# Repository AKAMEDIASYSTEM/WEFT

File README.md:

# WEFT
#### Experiments in electrovibration interaction strategies, inspired by Disney Research papers "Tesla Touch" and "Revel"

Here are the papers I am trying to implement here:
http://www.ivanpoupyrev.com/e-library/2010/teslatouchUIST2010.pdf

http://www.disneyresearch.com/wp-content/uploads/REVEL.pdf

### Summary
Basically, the papers describe a way to augment surfaces with _dynamically changeable tactile properties_ - a surface can change from sticky to slippery basically at will.

### Status
This work is incomplete and ongoing - for one thing, while the circuit decribed here works, I have yet to implement current-sensing feedback as described in the papers. I'm eager to accomplish this because it allows normalization of sensation across people, skin moistures, and time.

### Why I am interested
I'm interested in experimenting with this technology as applied to various notification strategies, particularly on mobile and wearable devices.
I would like to develop interactions in which a person queries a "stack" of stuff waiting for them, rather than being interrupted by a push notification.
The appeal of this technology in this application is that it's totally silent and able to be done without interrupting the person's conversation by stealing focus.
If this technology is implemented on the back of a mobile device, for example, simply rubbing a finger along the back of the phone is all that is needed to see the magnitude of my "stack."
Of course, "stack" can be many things: number of unread emails, number of to-do items, number of places of interest very near me, and so on.

### This repository
The purpose of this repo is to make my work shareable - I had a fair amount of trouble trying to go from the research paper to a safe, working circuit, and I'm hoping to save others some work.

The circuitboard isn't what I would put onto a phone - it is instead a platform for trying out different waveforms, intensities, and so on.

The intent is that you will use the board to figure out the correct implementation details and then generate your own board with a more appropriate layout.

### Requirements
You should follow the BOM pretty precisely unless you know what you are doing. The circuit is designed to work with a 9v battery and I will be trying to allow smaller/more power supplies to work with it. The microcontroller is a Teensy 3.1

### Thanks
I'm so grateful to Disney Research, Ivan Poupyrev, Olivier Bau, and others who worked on the papers for making their work available - I never would have known aobut this cool phoneomenon without their shared work! Thanks as well to nytlabs for supporting my explorations and letting me share in kind.

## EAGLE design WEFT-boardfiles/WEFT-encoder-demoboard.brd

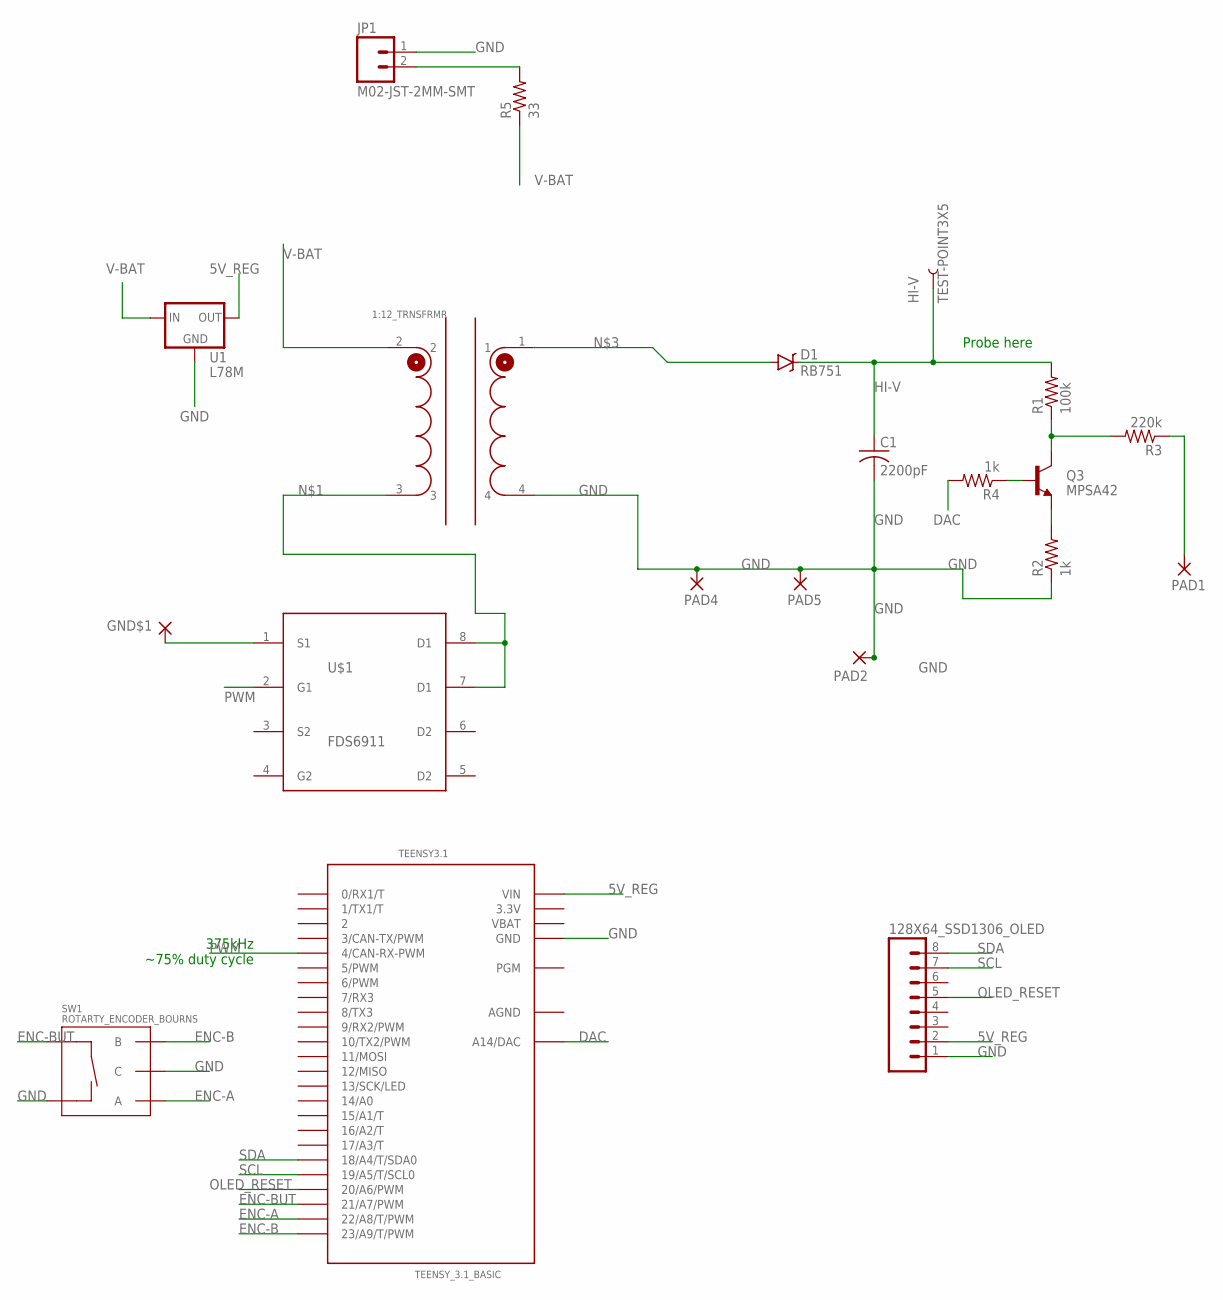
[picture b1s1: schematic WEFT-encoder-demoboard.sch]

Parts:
1:12_TRNSFRMR: PA0367
128X64_SSD1306_OLED: M08LOCK; 1X08_LOCK
C1: 2200pF; C1812
D1: RB751; TO263
GND$1: WIREPADSMD5-2,5; 5-2,5
HI-V: TEST-POINT3X5; PAD.03X.05
JP1: M02-JST-2MM-SMT; JST-2-SMD
PAD1, PAD2, PAD4, PAD5: WIREPADSMD5-2,5; 5-2,5
Q3: MPSA42; TO-92
R1: 100k; R2010
R2, R4: 1k; 1206
R3: 220k; R2010
R5: 33; 1206
SW1: ROTARTY_ENCODER_BOURNS; ROTARY_ENC_PLAIN_BOURNS
TEENSY3.1: TEENSY_3.1_BASIC
U1: L78M; DPAK
U$1: FDS6911; SO8

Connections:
3.3V: TEENSY3.1.3.3V
5V_REG: 128X64_SSD1306_OLED.2, TEENSY3.1.VIN, U1.3 (OUT)
AGND: TEENSY3.1.AGND
DAC: R4.2, TEENSY3.1.A14 (A14/DAC)
ENC-A: SW1.A, TEENSY3.1.22/A8 (22/A8/T/PWM)
ENC-B: SW1.B, TEENSY3.1.23/A9 (23/A9/T/PWM)
ENC-BUT: SW1.SW+, TEENSY3.1.21/A7 (21/A7/PWM)
GND: 1:12_TRNSFRMR.4, 128X64_SSD1306_OLED.1, C1.2, GND$1.1, JP1.1 (2), PAD2.1, PAD4.1, PAD5.1, R2.1, SW1.C, SW1.SW-, TEENSY3.1.GND, TEENSY3.1.GND1 (GND), U1.4 (GND), U$1.1 (S1)
HI-V: C1.1, D1.1 (C), HI-V.P$1, R1.2
unnamed: 1:12_TRNSFRMR.3, U$1.7 (D1), U$1.8 (D1)
unnamed: 1:12_TRNSFRMR.1, D1.2 (A)
unnamed: JP1.2 (1), R5.2
unnamed: Q3.1 (C), R1.1, R3.2
unnamed: Q3.3 (E), R2.2
unnamed: Q3.2 (B), R4.1
OLED_RESET: 128X64_SSD1306_OLED.5, TEENSY3.1.20/A6 (20/A6/PWM)
PAD: PAD1.1, R3.1
PWM: TEENSY3.1.4 (4/CAN-RX-PWM), U$1.2 (G1)
SCL: 128X64_SSD1306_OLED.7, TEENSY3.1.19/A5 (19/A5/T/SCL0)
SDA: 128X64_SSD1306_OLED.8, TEENSY3.1.18/A4 (18/A4/T/SDA0)
V-BAT: 1:12_TRNSFRMR.2, R5.1, U1.1 (IN)
VBAT: TEENSY3.1.VBAT

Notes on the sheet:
Probe here
375kHz ~75% duty cycle

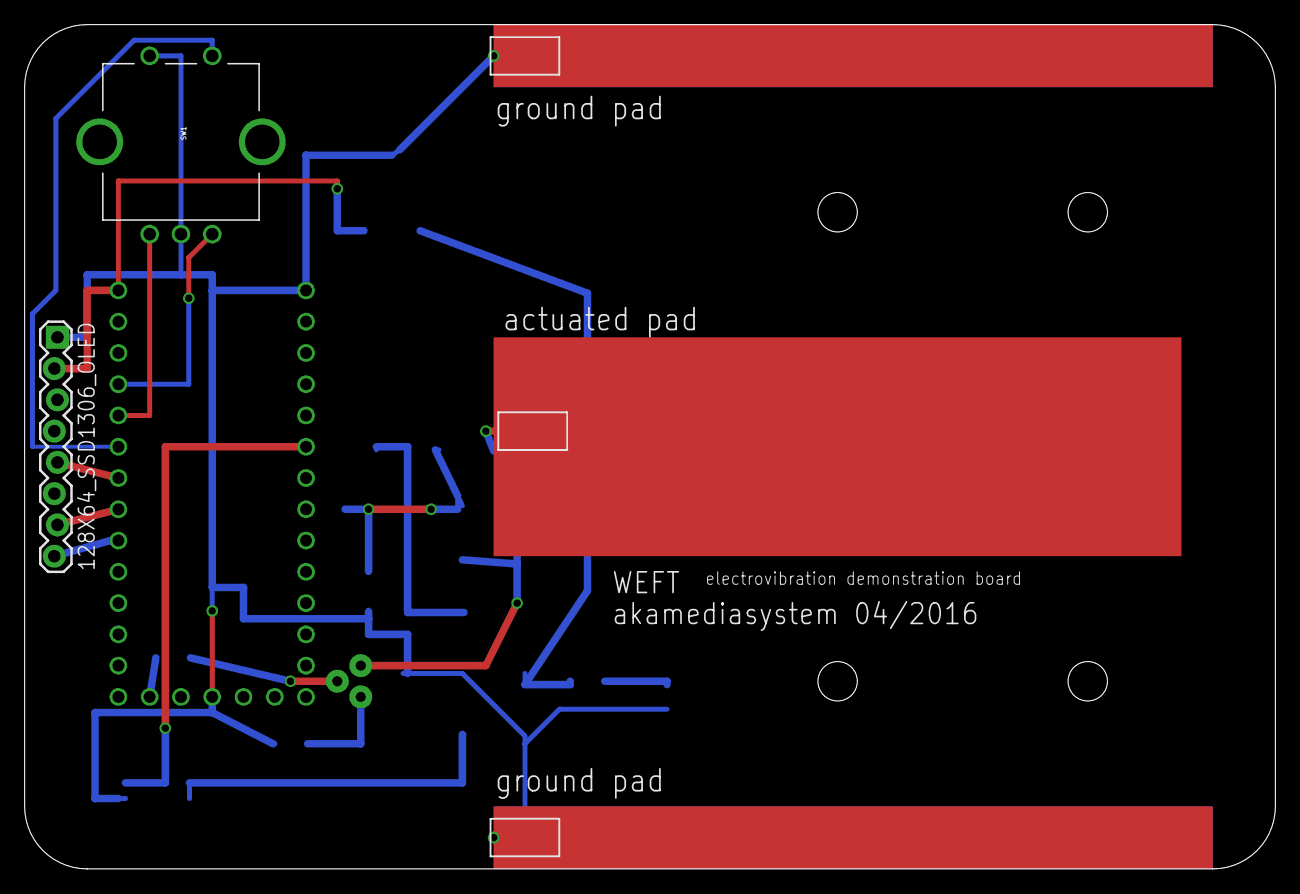
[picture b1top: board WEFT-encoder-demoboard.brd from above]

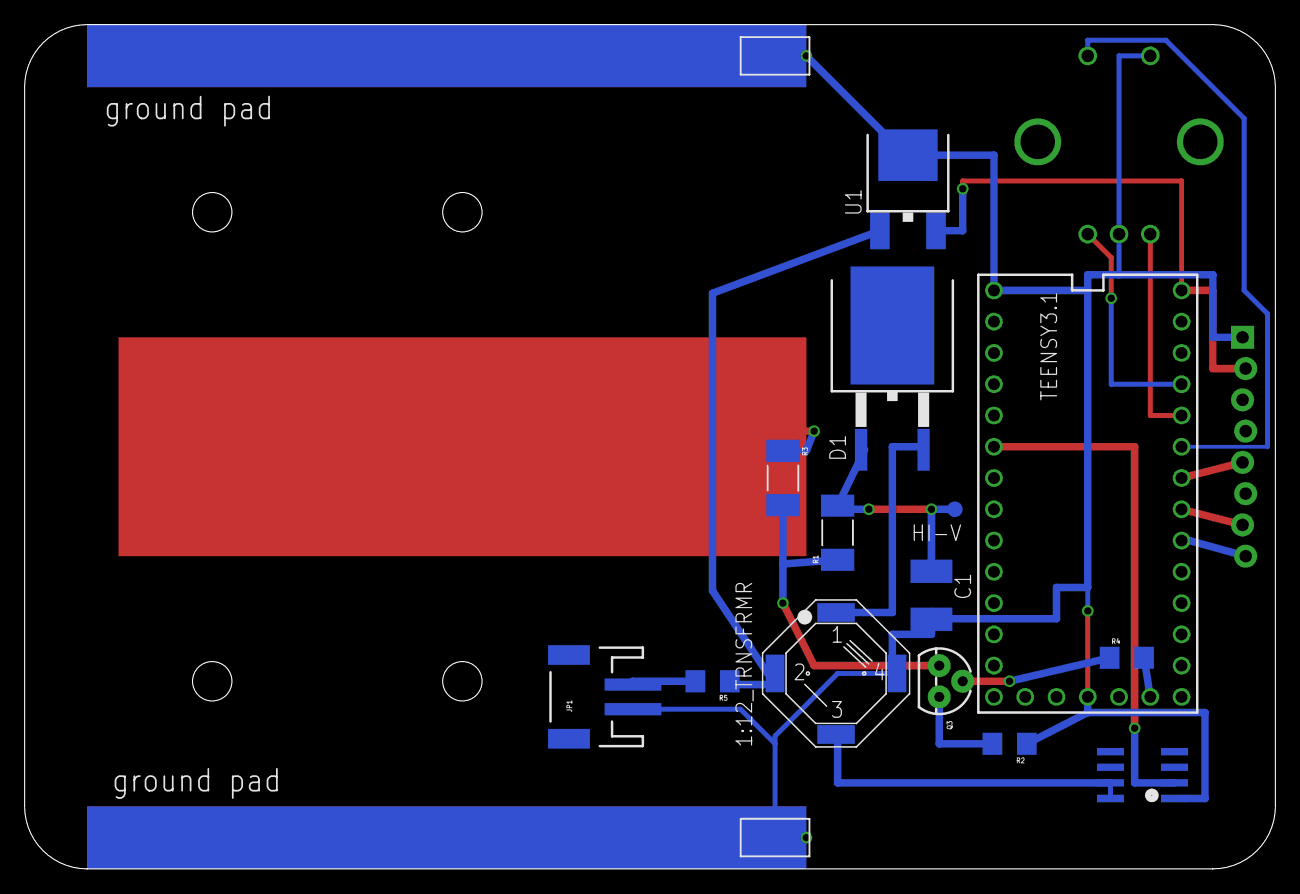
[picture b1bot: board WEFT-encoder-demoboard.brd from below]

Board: 2 copper layers, 101.6 x 68.6 mm, 21 parts (16 on the bottom side), 19 nets.

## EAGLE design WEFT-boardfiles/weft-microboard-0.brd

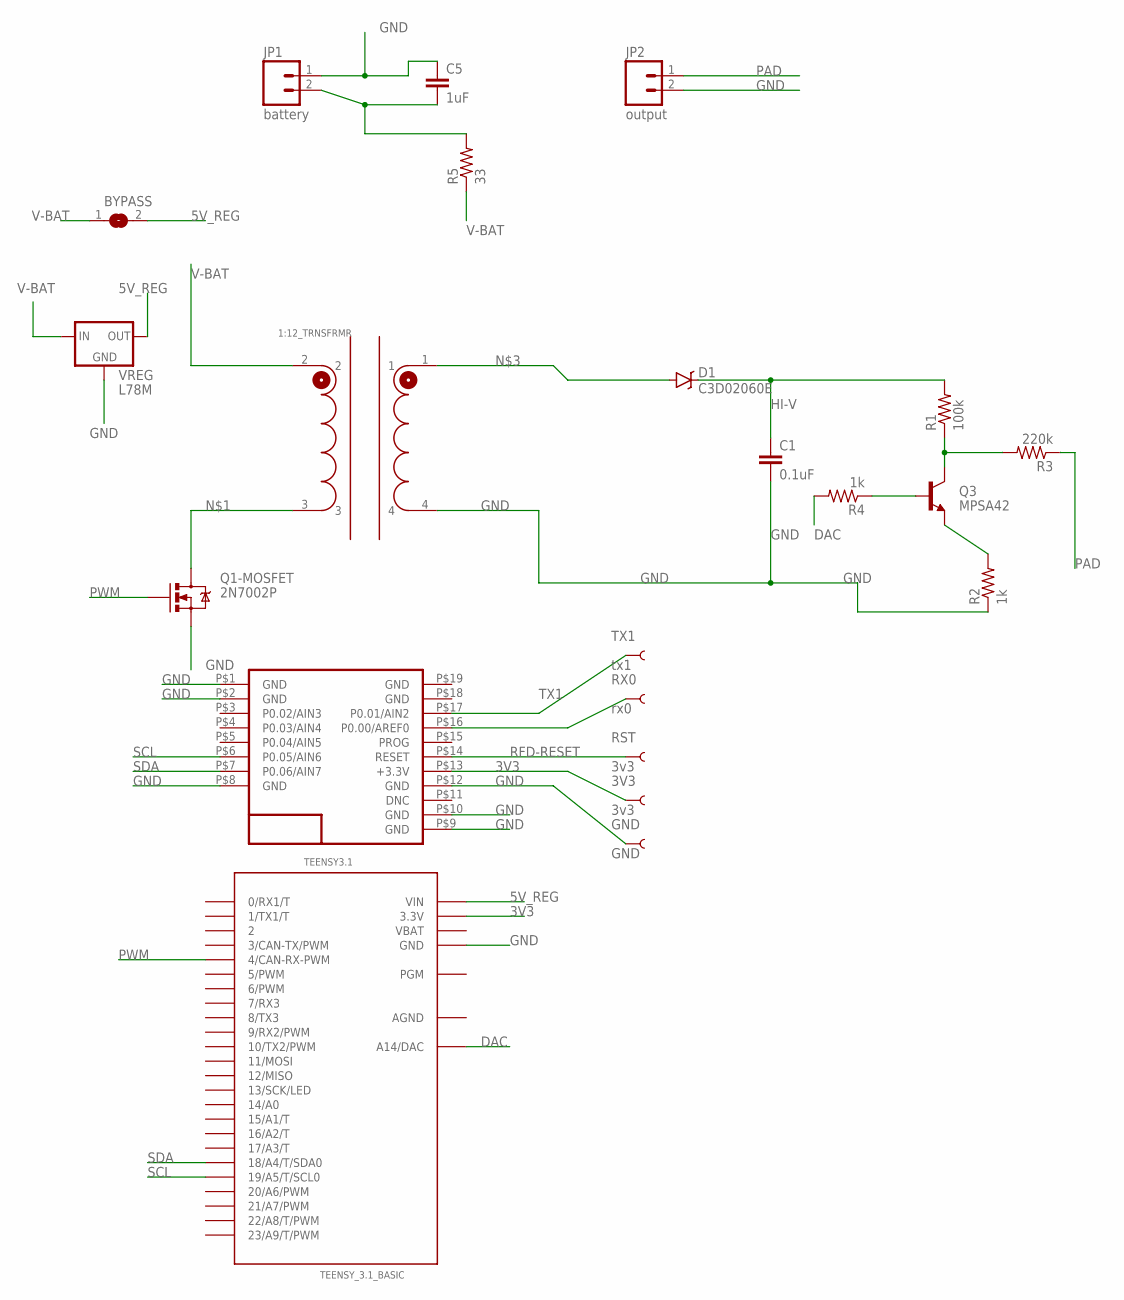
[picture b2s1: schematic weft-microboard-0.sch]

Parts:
1:12_TRNSFRMR: PA0367
3V3: 3v3; PAD.03X.03
BYPASS: SJ
C1: 0.1uF; 0805
C5: 1uF; 0805
D1: C3D02060E; TO252
GND: GND; PAD.03X.03
JP1: battery; JST-2-SMD
JP2: output; JST-2-SMD
Q1-MOSFET: 2N7002P; SOT23-3
Q3: MPSA42; SOT23-3
R1: 100k; 1206
R2, R4: 1k; 0805
R3: 220k; 1206
R5: 33; 0805
RFDUINO: RFD22301; RFD21733
RST: 3v3; PAD.03X.03
RX0: rx0; PAD.03X.03
TEENSY3.1: TEENSY_3.1_BASIC
TX1: tx1; PAD.03X.03
VREG: L78M; DPAK

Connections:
3V3: 3V3.P$1, RFDUINO.P$13 (+3.3V), TEENSY3.1.3.3V, TEENSY3.1.3.3V1 (3.3V)
5V_REG: BYPASS.2, TEENSY3.1.VIN, VREG.3 (OUT)
AGND: TEENSY3.1.AGND
DAC: R4.2, TEENSY3.1.A14 (A14/DAC)
EMIT: Q3.2 (E), R2.2
GND: 1:12_TRNSFRMR.4, C1.2, C5.1, GND.P$1, JP1.1 (2), JP2.2 (1), Q1-MOSFET.2 (S), R2.1, RFDUINO.P$1 (GND), RFDUINO.P$2 (GND), RFDUINO.P$8 (GND), RFDUINO.P$9 (GND), RFDUINO.P$10 (GND), RFDUINO.P$12 (GND), TEENSY3.1.GND, TEENSY3.1.GND1 (GND), VREG.4 (GND)
HI-V: C1.1, D1.1 (C), R1.2
unnamed: 1:12_TRNSFRMR.3, Q1-MOSFET.3 (D)
unnamed: RFDUINO.P$16 (P0.00/AREF0), RX0.P$1
unnamed: 1:12_TRNSFRMR.1, D1.2 (A)
unnamed: C5.2, JP1.2 (1), R5.2
unnamed: Q3.3 (C), R1.1, R3.2
unnamed: Q3.1 (B), R4.1
PAD: JP2.1 (2), R3.1
PWM: Q1-MOSFET.1 (G), TEENSY3.1.4 (4/CAN-RX-PWM)
RFD-RESET: RFDUINO.P$14 (RESET), RST.P$1
SCL: RFDUINO.P$6 (P0.05/AIN6), TEENSY3.1.19/A5 (19/A5/T/SCL0)
SDA: RFDUINO.P$7 (P0.06/AIN7), TEENSY3.1.18/A4 (18/A4/T/SDA0)
TX1: RFDUINO.P$17 (P0.01/AIN2), TX1.P$1
V-BAT: 1:12_TRNSFRMR.2, BYPASS.1, R5.1, VREG.1 (IN)
VBAT: TEENSY3.1.VBAT

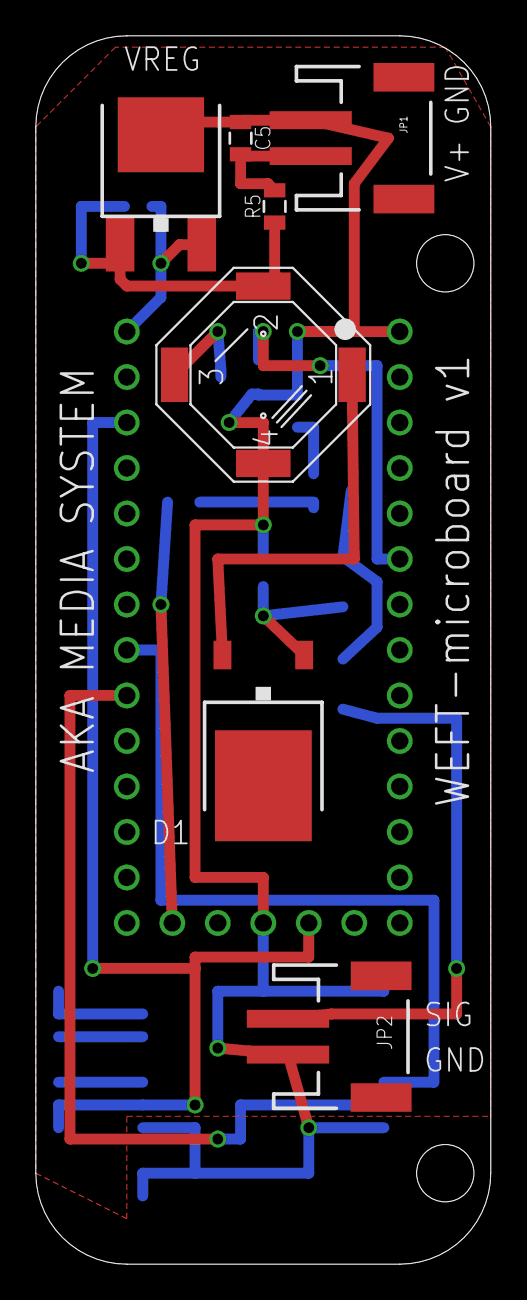
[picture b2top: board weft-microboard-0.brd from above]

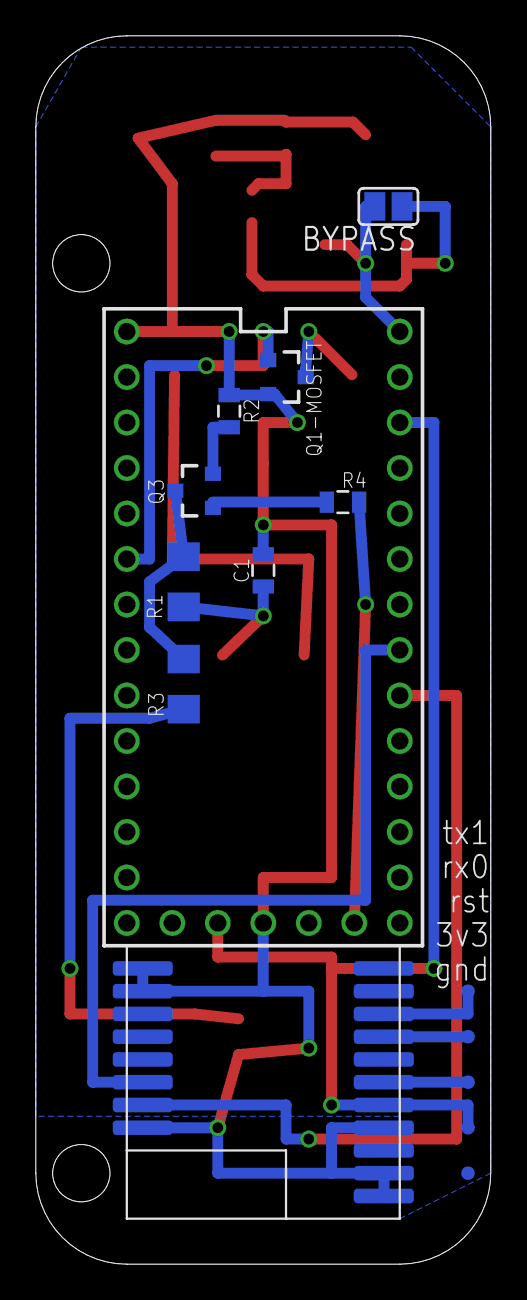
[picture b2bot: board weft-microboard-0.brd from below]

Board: 2 copper layers, 25.4 x 68.6 mm, 22 parts (15 on the bottom side), 19 nets.

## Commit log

2015-11-15 first commit to new repo
2015-11-15 added readme
2015-11-23 cleanup teensy slave code, prepare to add android app to repo
2015-11-23 adding CAD and android files, not much CAD yet
2015-11-23 un-screwed the android code after dropbox marked all my work as 'conflicted'. Now able to connect to WEFT and use UI elements to alter signal properties
2015-11-23 logo
2015-12-04 cleanup and one debug statement
2015-12-13 rev of weftboard and tweak firmware
2015-12-21 android app updates, debugging and notifications integration
2016-01-05 small changes
2016-01-11 added mit license
2016-01-12 simplifying this app for testing with hobby board
2016-04-26 adding an encoder-ready demo board, not yet completed, and also adding photos
2017-07-26 small update

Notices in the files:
parts and their libraries:
SparkFun-DiscreteSemi: Licensing: Creative Commons ShareAlike 4.0 International - https://creativecommons.org/licenses/by-sa/4.0
